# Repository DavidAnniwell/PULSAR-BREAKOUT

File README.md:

# PULSAR-BREAKOUT
HD68 to 3 2x12 Terminal Block PCB for the Pulsar Timing System

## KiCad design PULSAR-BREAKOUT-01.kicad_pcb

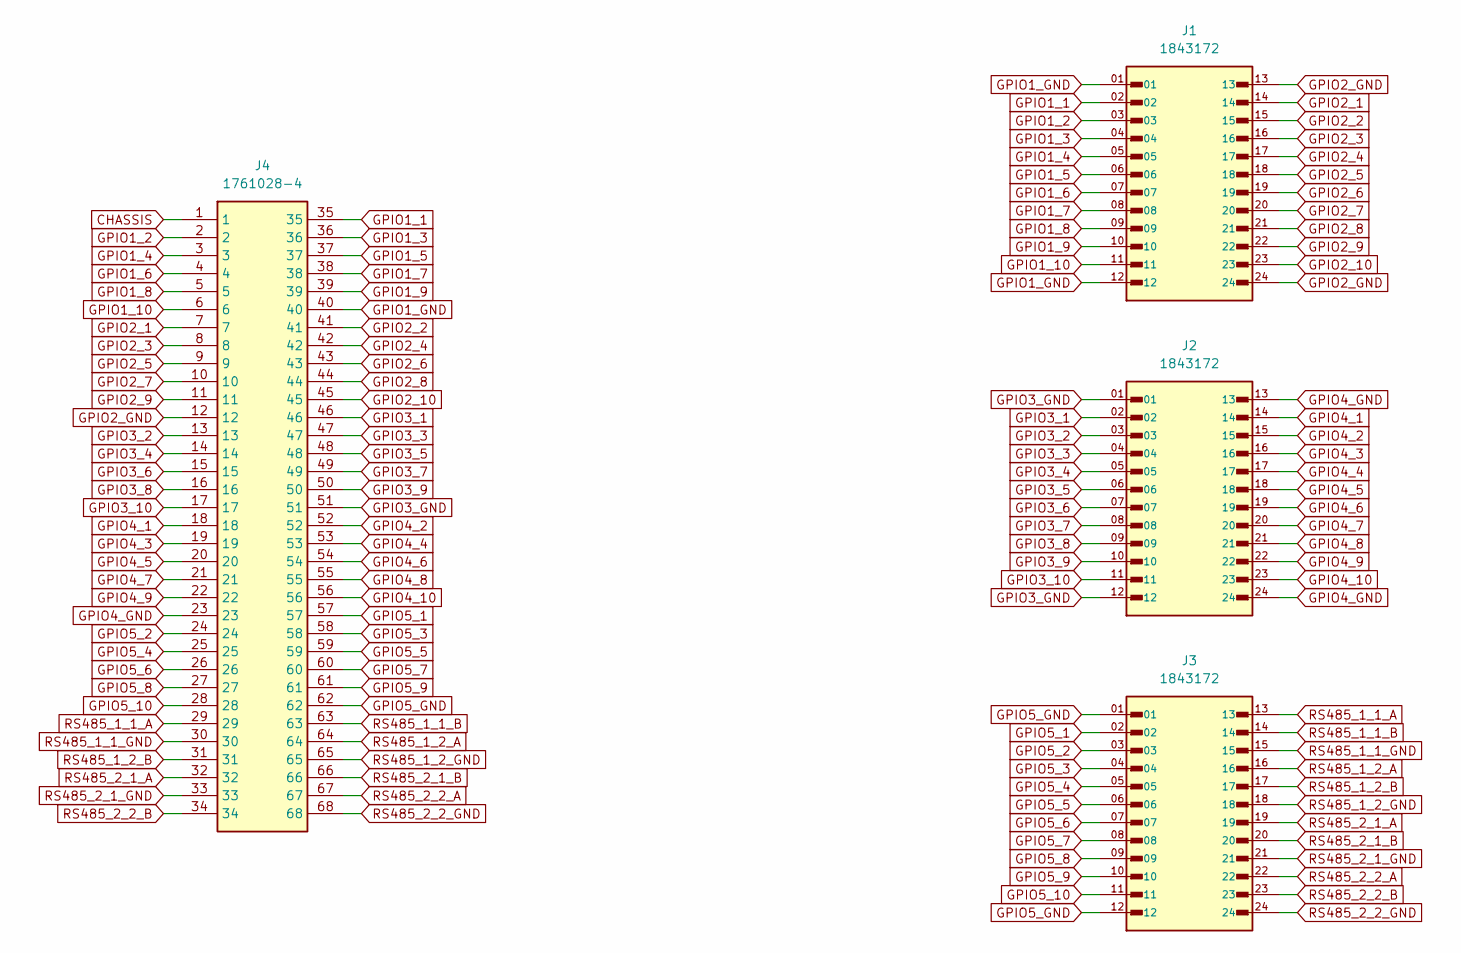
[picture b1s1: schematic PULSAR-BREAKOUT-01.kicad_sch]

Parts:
J1, J2, J3: 1843172; PHOENIX_1843172; PARTREV 12.06.2015
J4: 1761028-4; Manufacturer_Part_Number 1761028-4

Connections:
CHASSIS: J4.1, J4.69, J4.70
GPIO1_1: J1.02, J4.35
GPIO1_2: J1.03, J4.2
GPIO1_3: J1.04, J4.36
GPIO1_4: J1.05, J4.3
GPIO1_5: J1.06, J4.37
GPIO1_6: J1.07, J4.4
GPIO1_7: J1.08, J4.38
GPIO1_8: J1.09, J4.5
GPIO1_9: J1.10, J4.39
GPIO1_10: J1.11, J4.6
GPIO1_GND: J1.01, J1.12, J4.40
GPIO2_1: J1.14, J4.7
GPIO2_2: J1.15, J4.41
GPIO2_3: J1.16, J4.8
GPIO2_4: J1.17, J4.42
GPIO2_5: J1.18, J4.9
GPIO2_6: J1.19, J4.43
GPIO2_7: J1.20, J4.10
GPIO2_8: J1.21, J4.44
GPIO2_9: J1.22, J4.11
GPIO2_10: J1.23, J4.45
GPIO2_GND: J1.13, J1.24, J4.12
GPIO3_1: J2.02, J4.46
GPIO3_2: J2.03, J4.13
GPIO3_3: J2.04, J4.47
GPIO3_4: J2.05, J4.14
GPIO3_5: J2.06, J4.48
GPIO3_6: J2.07, J4.15
GPIO3_7: J2.08, J4.49
GPIO3_8: J2.09, J4.16
GPIO3_9: J2.10, J4.50
GPIO3_10: J2.11, J4.17
GPIO3_GND: J2.01, J2.12, J4.51
GPIO4_1: J2.14, J4.18
GPIO4_2: J2.15, J4.52
GPIO4_3: J2.16, J4.19
GPIO4_4: J2.17, J4.53
GPIO4_5: J2.18, J4.20
GPIO4_6: J2.19, J4.54
GPIO4_7: J2.20, J4.21
GPIO4_8: J2.21, J4.55
GPIO4_9: J2.22, J4.22
GPIO4_10: J2.23, J4.56
GPIO4_GND: J2.13, J2.24, J4.23
GPIO5_1: J3.02, J4.57
GPIO5_2: J3.03, J4.24
GPIO5_3: J3.04, J4.58
GPIO5_4: J3.05, J4.25
GPIO5_5: J3.06, J4.59
GPIO5_6: J3.07, J4.26
GPIO5_7: J3.08, J4.60
GPIO5_8: J3.09, J4.27
GPIO5_9: J3.10, J4.61
GPIO5_10: J3.11, J4.28
GPIO5_GND: J3.01, J3.12, J4.62
RS485_1_1_A: J3.13, J4.29
RS485_1_1_B: J3.14, J4.63
RS485_1_1_GND: J3.15, J4.30
RS485_1_2_A: J3.16, J4.64
RS485_1_2_B: J3.17, J4.31
RS485_1_2_GND: J3.18, J4.65
RS485_2_1_A: J3.19, J4.32
RS485_2_1_B: J3.20, J4.66
RS485_2_1_GND: J3.21, J4.33
RS485_2_2_A: J3.22, J4.67
RS485_2_2_B: J3.23, J4.34
RS485_2_2_GND: J3.24, J4.68

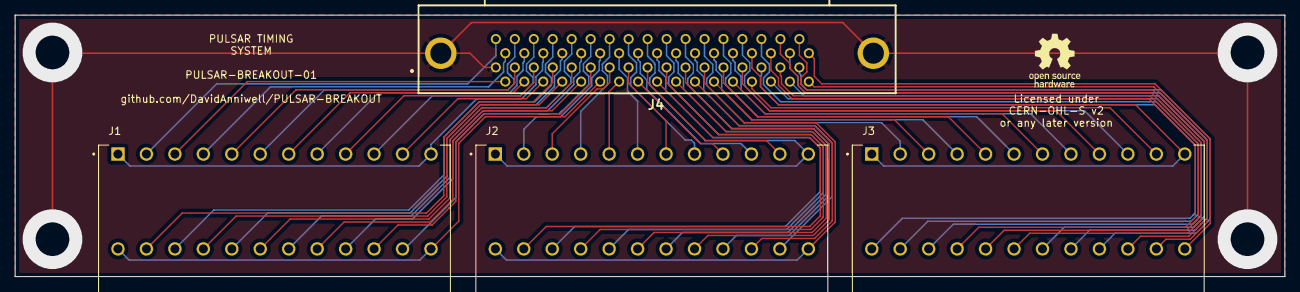
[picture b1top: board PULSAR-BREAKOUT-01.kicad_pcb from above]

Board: 2 copper layers, 170.0 x 35.0 mm, 4 parts (0 on the bottom side), 68 nets.

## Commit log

2024-08-10 Create LICENSE
2024-08-10 Add files via upload
    Initial commit

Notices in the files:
PULSAR-BREAKOUT-01.kicad_pcb:
Licensed under
CERN-OHL-S v2
Copyright David Anniwell 2024.
This source describes Open Hardware and is licensed under the CERN-
under the terms of the CERN-OHL-S v2
(https://ohwr.org/cern ohl s v2.txt ).
QUALITY AND FITNESS FOR A PARTICULAR PURPOSE. Please see
the CERN-OHL-S v2 for applicable conditions.
As per CERN-OHL-S v2 section 4, should You produce hardware based
